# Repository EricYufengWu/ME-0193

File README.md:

### Repository for ME0193

P2 is done!

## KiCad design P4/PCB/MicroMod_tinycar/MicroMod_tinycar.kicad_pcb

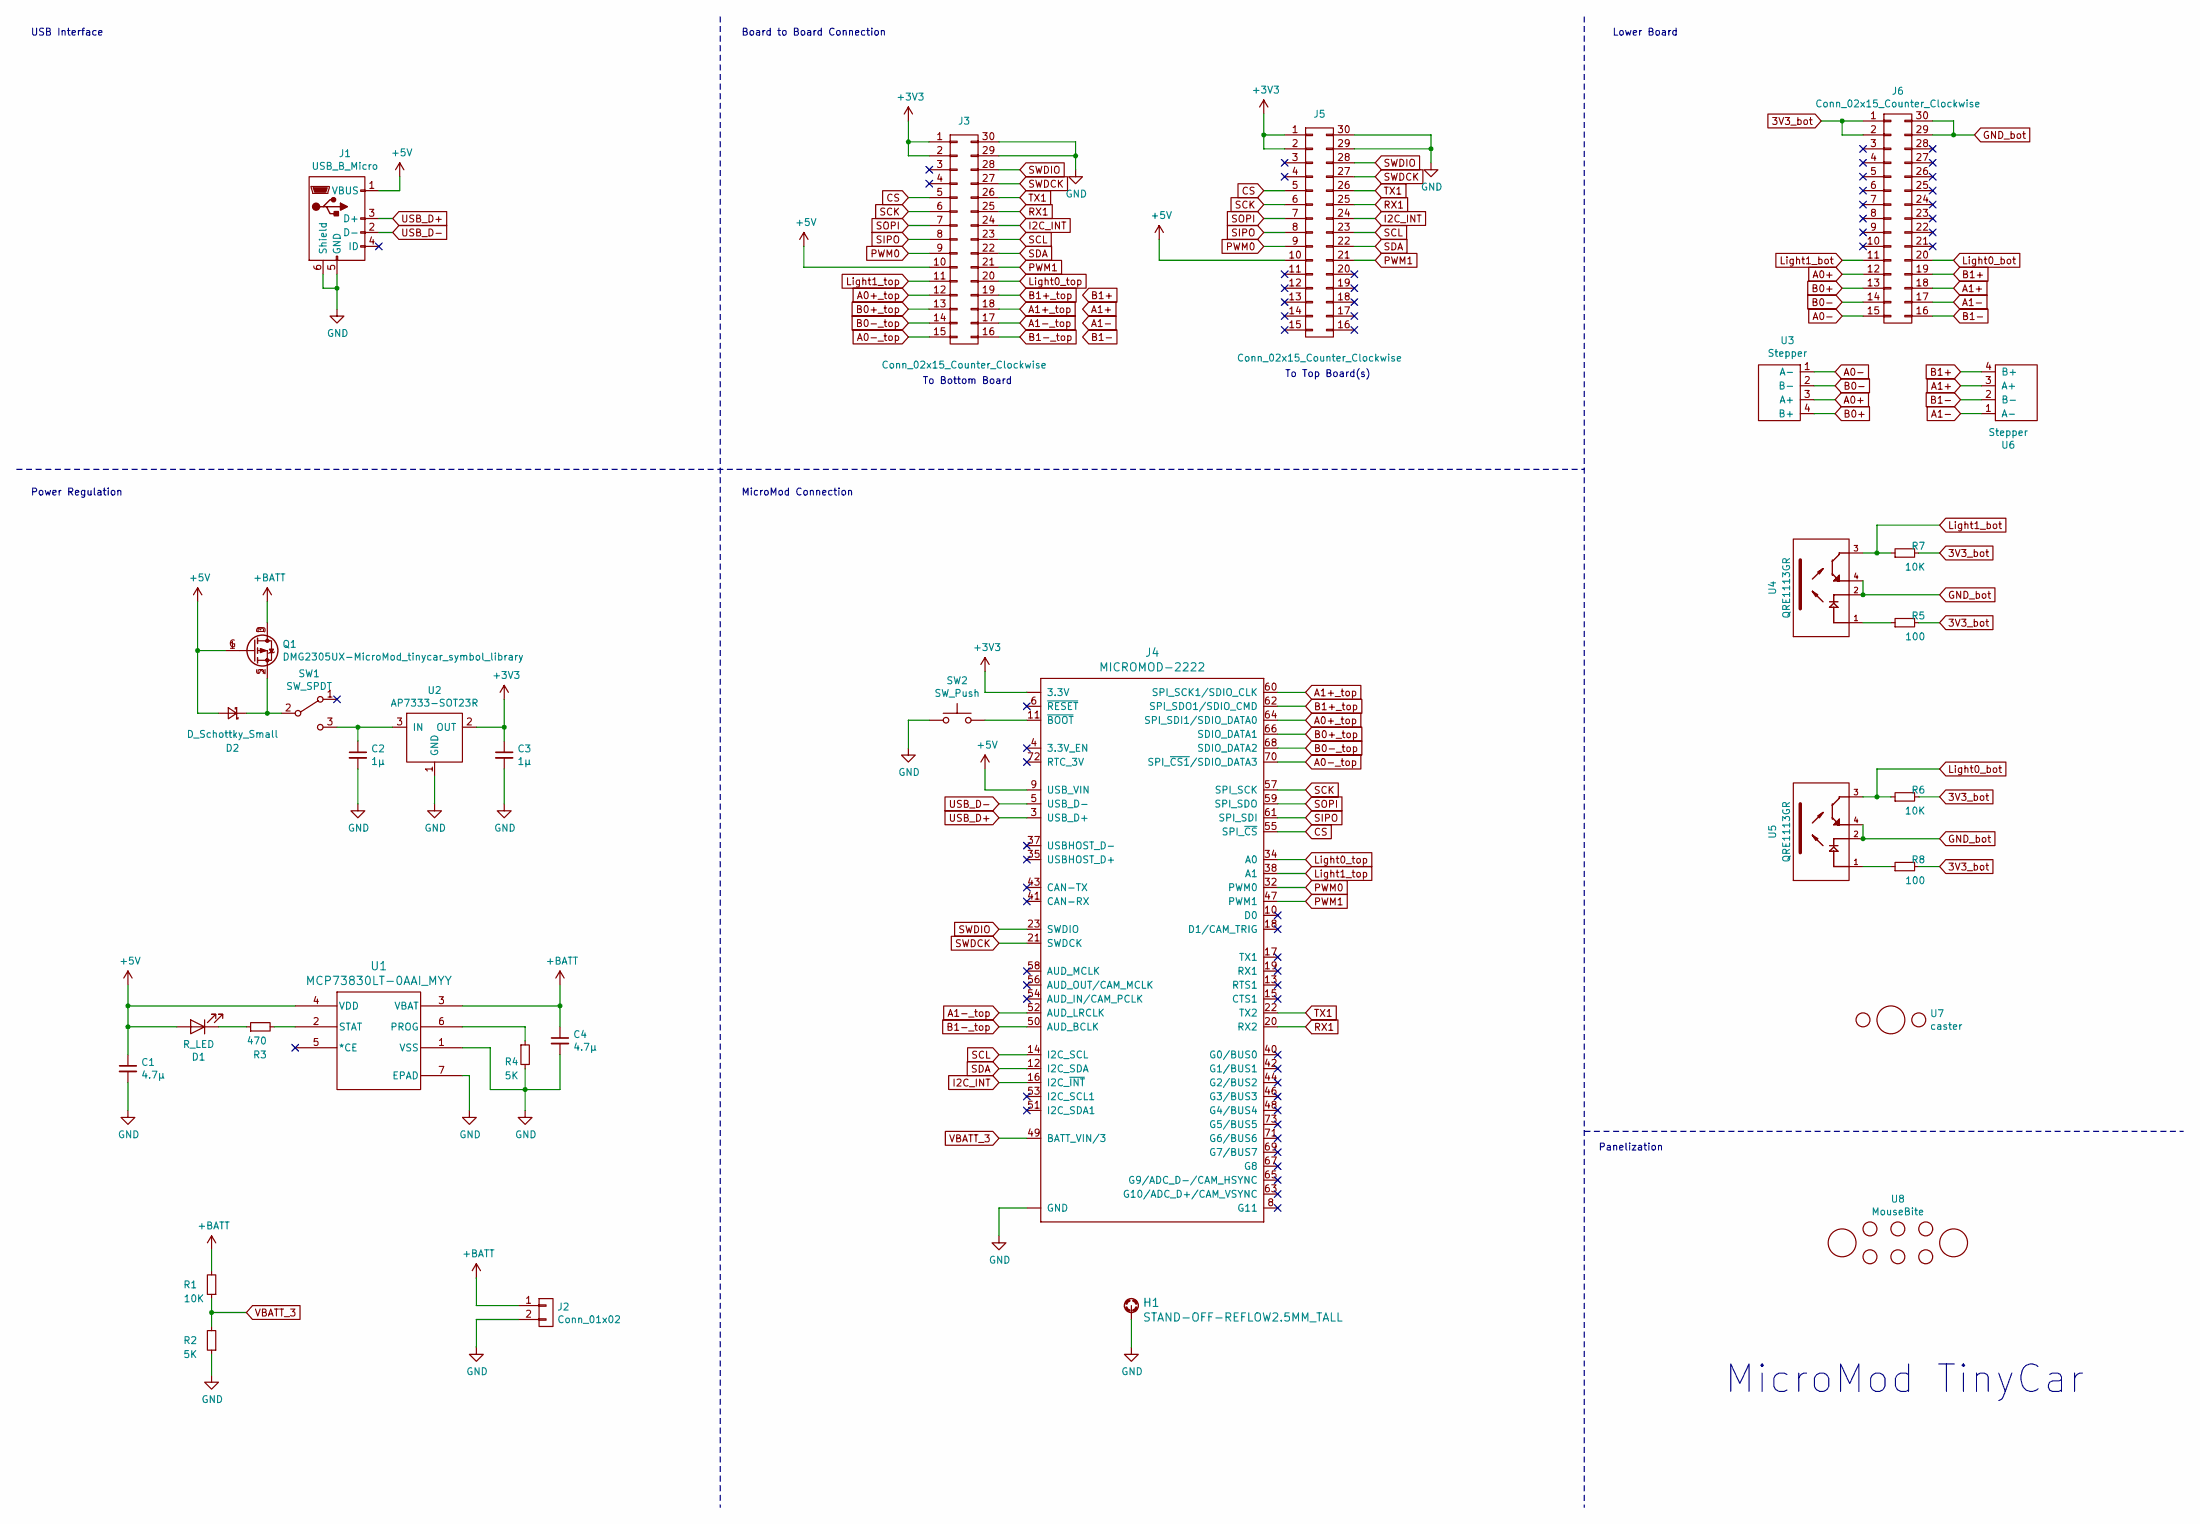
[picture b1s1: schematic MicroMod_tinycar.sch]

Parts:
C1, C4: 4.7μ; C_0805_2012Metric
C2, C3: 1μ; C_0805_2012Metric
D1: R_LED; LED_0805_2012Metric
D2: D_Schottky_Small; D_0805_2012Metric
H1: STAND-OFF-REFLOW2.5MM_TALL; STAND-OFF-REFLOW-M2.5
J1: USB_B_Micro; USB_Micro-B_Molex_47346-0001
J2: Conn_01x02; JST_PH_S2B-PH-K_1x02_P2.00mm_Horizontal
J3, J6: Conn_02x15_Counter_Clockwise; Bottom_adapter
J4: MICROMOD-2222; M.2-CONNECTOR-E
J5: Conn_02x15_Counter_Clockwise; Top_adapter
Q1: DMG2305UX-MicroMod_tinycar_symbol_library; DMG2305UX_SOT-23
R1, R6, R7: 10K; R_0805_2012Metric
R2, R4: 5K; R_0805_2012Metric
R3: 470; R_0805_2012Metric
R5, R8: 100; R_0805_2012Metric
SW1: SW_SPDT; SW_PCM12SMTR
SW2: SW_Push; SW_TL1015AF160QG
U1: MCP73830LT-0AAI_MYY; MCP73830LT-0AAI&slash_MYY
U2: AP7333-SOT23R; AP7333_SOT-23
U3, U6: Stepper; Mini_Stepper
U4, U5: QRE1113GR; PARTREV 5
U7: caster; tiny_caster
U8: MouseBite; mouse-bite-2.54mm-slot

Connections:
3V3_bot: J6.1, J6.2, R5.2, R6.2, R7.2, R8.2
+3V3: C3.1, J3.1, J3.2, J4.2 (3.3V), J4.74 (3.3V), J5.1, J5.2, U2.2 (OUT)
+5V: C1.1, D1.2 (A), D2.2 (A), J1.1 (VBUS), J3.10, J4.9 (USB_VIN), J5.10, Q1.1 (G), U1.4 (VDD)
+BATT: C4.1, J2.1 (+), Q1.3 (D), R1.2, U1.3 (VBAT)
A0+: J6.12, U3.3 (A+)
A0+_top: J3.12, J4.64 (SPI_SDI1/SDIO_DATA0)
A0-: J6.15, U3.1 (A-)
A0-_top: J3.15, J4.70 (SPI_~CS1~/SDIO_DATA3)
A1+: J6.18, U6.3 (A+)
A1+_top: J3.18, J4.60 (SPI_SCK1/SDIO_CLK)
A1-: J6.17, U6.1 (A-)
A1-_top: J3.17, J4.52 (AUD_LRCLK)
B0+: J6.13, U3.4 (B+)
B0+_top: J3.13, J4.66 (SDIO_DATA1)
B0-: J6.14, U3.2 (B-)
B0-_top: J3.14, J4.68 (SDIO_DATA2)
B1+: J6.19, U6.4 (B+)
B1+_top: J3.19, J4.62 (SPI_SDO1/SDIO_CMD)
B1-: J6.16, U6.2 (B-)
B1-_top: J3.16, J4.50 (AUD_BCLK)
CS: J3.5, J4.55 (SPI_~CS~), J5.5
GND: C1.2, C2.2, C3.2, C4.2, H1.1, J1.5 (GND), J1.6 (Shield), J2.2 (-), J3.29, J3.30, J4.1 (GND), J4.7 (GND), J4.33 (GND), J4.36 (GND), J4.39 (GND), J4.45 (GND), J4.75 (GND), J4.GND1 (GND), J4.GND2 (GND), J4.GND3 (GND), J5.29, J5.30, R2.1, R4.2, SW2.1, U1.1 (VSS), U1.7 (EPAD), U2.1 (GND)
GND_bot: J6.29, J6.30, U4.2, U4.4, U5.2, U5.4
I2C_INT: J3.24, J4.16 (I2C_~INT~), J5.24
Light0_bot: J6.20, R6.1, U5.3
Light0_top: J3.20, J4.34 (A0)
Light1_bot: J6.11, R7.1, U4.3
Light1_top: J3.11, J4.38 (A1)
unnamed: C2.1, SW1.3 (C), U2.3 (IN)
unnamed: D1.1 (K), R3.1
unnamed: D2.1 (K), Q1.2 (S), SW1.2 (B)
unnamed: J4.11 (~BOOT~), SW2.2
unnamed: R3.2, U1.2 (STAT)
unnamed: R4.1, U1.6 (PROG)
unnamed: R5.1, U4.1
unnamed: R8.1, U5.1
PWM0: J3.9, J4.32 (PWM0), J5.9
PWM1: J3.21, J4.47 (PWM1), J5.21
RX1: J3.25, J4.20 (RX2), J5.25
SCK: J3.6, J4.57 (SPI_SCK), J5.6
SCL: J3.23, J4.14 (I2C_SCL), J5.23
SDA: J3.22, J4.12 (I2C_SDA), J5.22
SIPO: J3.8, J4.61 (SPI_SDI), J5.8
SOPI: J3.7, J4.59 (SPI_SDO), J5.7
SWDCK: J3.27, J4.21 (SWDCK), J5.27
SWDIO: J3.28, J4.23 (SWDIO), J5.28
TX1: J3.26, J4.22 (TX2), J5.26
USB_D+: J1.3 (D+), J4.3 (USB_D+)
USB_D-: J1.2 (D-), J4.5 (USB_D-)
VBATT_3: J4.49 (BATT_VIN/3), R1.1, R2.2

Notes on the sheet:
To Bottom Board
To Top Board(s)
USB Interface
Power Regulation
Board to Board Connection
MicroMod Connection
Lower Board
Panelization
MicroMod TinyCar

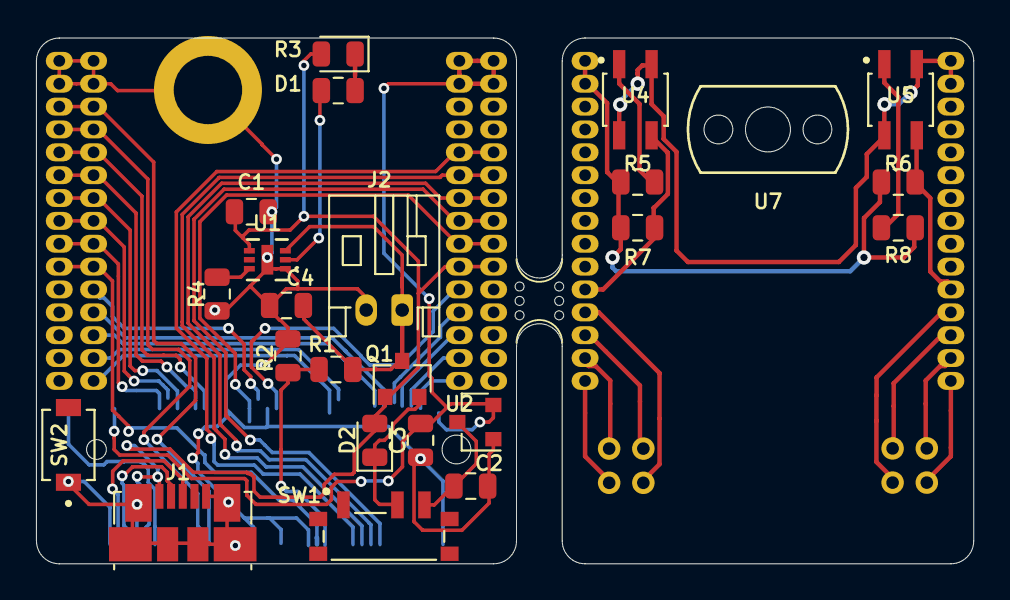
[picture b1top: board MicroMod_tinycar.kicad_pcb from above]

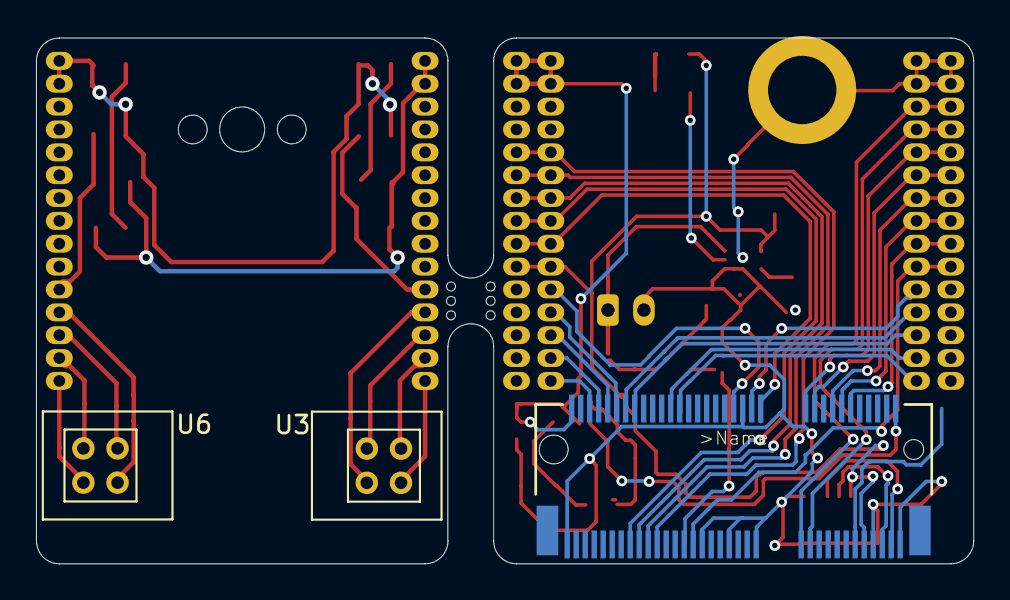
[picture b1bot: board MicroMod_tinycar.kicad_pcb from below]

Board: 2 copper layers, 52.1 x 29.2 mm, 32 parts (5 on the bottom side), 50 nets.

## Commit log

2021-02-03 initialization
2021-02-21 2nd level
2021-02-22 complete v1
2021-03-01 p2 final
2021-03-01 finished p2
2021-03-07 added p3
2021-03-07 2D basic computation
2021-03-09 symbolic 3D
2021-03-09 failed 3D...
2021-03-10 basic two methods
2021-03-11 Basic IK done
2021-03-11 ready for submission
2021-03-11 fixed plot
2021-03-11 updated fast_ik sweep function
2021-03-16 added P4 readme
2021-03-22 reorganized things
2021-03-30 p4 version1 pcb
2021-03-31 done with P4
2021-04-20 finished P4
2021-04-20 started P6
2021-06-08 P5 Done

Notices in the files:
parts and their libraries:
Copyright 2016 Accelerated Designs. All rights reserved.
